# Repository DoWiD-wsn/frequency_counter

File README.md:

# AVR-based Frequency Counter

The AVR-based frequency counter is partly based on the project developed by [Herbert Dingfelder](http://www.herbert-dingfelder.de/?page_id=304) with some extensions and modifications.
It contains an ATmega8 responsible for measuring the frequency of a square-wave applied to one of four input channels (selectable by software) and acting as a TWI slave (I2C).
With the current design, frequencies of up to 50 MHz are measurable with a precision of 10 Hz.

The AVR-based frequency counter was developed and used as part of the [Embedded Testbench (ETB)](https://github.com/DoWiD-wsn/embedded_testbench) where it was used to measure the frequency stability of the internal clock of microcontroller units of embedded systems under different conditions such as ambient temperature and supply voltage level.

For more information on the PCB (and its design) refer to [docs/pcb_design.md](docs/pcb_design.md).

## Directory structure

```
.
├── docs                : documents
│   ├── datasheets      : datasheets of used components
│   └── pcb_design.md   : information on the PCB design
├── kicad               : KiCad files
├── media               : Miscellaneous media (images, etc.)
│   ├── evaluation      : Image of a first prototype evaluation
│   ├── i2c             : I2C register format
│   ├── pcb             : Photos and rendered images of the PCB
│   └── schematic       : SVG images of the schematics
└── source              : C code sources for the ATmega8
```

## Contents

* [Description](#description)
* [Built with](#built-with)
* [Preparation](#preparation)
* [I2C Interface](#i2c-interface)
* [Evaluation](#evaluation)
* [Contributors](#contributors)
* [Changelog](#changelog)
* [License](#license)

## Description

**Schematic** (draft):  

The ATmega8 is clocked with an external quartz crystal with a frequency of 4.096 MHz.
This clock signal is also used to generate a gate-enable signal for the actual frequency counting stage.
To do so, the 4.096 MHz are first divided by a 74HC4040 with a factor of 2^12 (4096) to get a 1 kHz signal that is further divided by a second 74HC4040 with a factor of 2^8 (256) to have an enable signal with a frequency of 3.90625 Hz (corresponds to an enable time of 128 ms (high level)).

The 74HC153 is used to select between four different input channels.
During the 128 ms long high period of the second 74HC4040, the signal of at the selected input channel is forwarded to the third 74HC4040.
That third 74HC4040 forms together with the ATmega8 the actual counting part, that is, both components together form a 24-bit counter that counts the number of periods of the selected input signal during the 128 ms long enable period.
Thereby, the lower 8-bit (fast portion) are counted by the 74HC4040 and, since the eight bit (Q7) triggers the ATmega8' internal 16-bit counter module, the higher 16-bit are counted internally by the ATmega8.
As the 128 ms enable signal is also connected to the external interrupt (INT0) of the ATmega8, the ATmega8 is "informed" whenever a counting period has finished and can then calculate the corresponding frequency of the input signal.
To do so, the 24-bit counter (lower 8-bit read via GPIOs and the higher 16-bit available interally) show how many periods have passed in the last 128 ms and, thus, allow to easily calculate the resulting frequency.

The measured frequency is output via the UART debug interface (default: 8N1 @9600baud).
As the ATmega8 is configured as an I2C slave (address to be defined in software; default: `0x24`), the result can also be obtained via I2C.
Additionally, the I2C interface can be used to configure the basic operation of the frequency counter such as:

* result resolution (Hz, kHz, or MHz)
* input channel (CH0, CH1, CH2, or CH3)
* sampling rate (no sampling, 3 samples, 5 samples, or 10 samples)

Additionally, the result ready flag can be read indicating whether a result is already available.
In case required, also a counter reset (clearing of all registers) can be requested via I2C.

## Built with

The entire code only depends on the basic AVR libraries (i.e., AVR libc) and can be easily compiled with the AVR GCC.
To upload the binary to the ATmega8, the [AVR-ISP](https://www.mikrocontroller.net/articles/AVR_In_System_Programmer) can be used in combination with [AVRdude](https://www.nongnu.org/avrdude/) or similar.

* [avr-gcc 5.4.0](https://gcc.gnu.org/wiki/avr-gcc) - C code library
* [avr-libc 2.0.0](https://www.nongnu.org/avr-libc/) - C code library

## Preparation

Aside from the hardware circuit, it is important to properly set the fuses of the used ATmega8.
The fuses take care of a basic configuration of the ATmega8, or more precisely, they define the clock source and some interfacing options.
For the AVR-based frequency counter, we choose to have an external crystal oscillator and at startup we will give it some clock cycles to become stable.
As stated in the [ATmega8 datasheet](https://www.microchip.com/wwwproducts/en/ATmega8), we need to have the clock selection fuses `CKSEL` set to `1111` and the start-up times fuses `SUT` set to `11`, resulting in the `low fuse byte` to be set to `0xFF` (Note: the fuse bits are active low, i.e. programmed=0, unprogrammed=1; see also [AVR Fuse Calculator](http://eleccelerator.com/fusecalc/fusecalc.php?chip=atmega8)).

In the `high fuse byte`, we leave the boot size selection bits enabled, i.e., `BOOTSZ` is `00`, and we keep the serial programming and data downloading `SPIEN` enabled (otherwise we would not be able to use the [AVR ISP](https://www.mikrocontroller.net/articles/AVR_In_System_Programmer) to flash our firmware).
Additionally, we need to program the oscillator options fuse `CKOPT` to `0` to switch the crystal from weak amplitude to full amplitude required to clock the [74HC4040](https://www.ti.com/product/SN74HC4040) counter.
As a result, we need to set the `high fuse byte` to `0xC9`.

The fuse bit values and the resulting bit pattern as well as the corresponding [AVRDUDE](https://www.nongnu.org/avrdude/) commands can be derived with one of the available [online fuse calculator](https://www.engbedded.com/fusecalc/).
In our case, the resulting AVRDUDE arguments are:  
  `-U lfuse:w:0xff:m -U hfuse:w:0xc9:m`

## I2C Interface

The AVR-based frequency counter can be used as an I2C slave.
The I2C address can be defined in software (default: 0x24).

Basically, there are four 8-bit registers available and accessible via I2C, that are:

1. Configuration register `CONFIG` (address: `0x00`; R/W)
2. Frequency LSB register `FREQ-LSB` (address: `0x01`; R)
3. Frequency MSB register `FREQ-MSB` (address: `0x02`; R)
4. Frequency extended MSB register `FREQ-XMSB` (address: `0x03`; R)

As can be seen, all registers can be read but only the `CONFIG` register allows overwriting its value; the measured frequency value can only be read.

With the `CONFIG` register, the basic operation of the frequency counter can be defined, that is, requesting a software reset, checking the result ready flag, setting the sampling rate, defining the frequency resolution, and selecting the input channel (see figure below).
The default value of the `CONFIG` register is `0x00`.

### Reset request

The reset request bit can be used to cause a software reset of the frequency counter, that is, all counter modules and internal counter values are reset.
The configuration is not changed.

| `RST` | Effect        |
|-------|---------------|
| `0`   | no effect     |
| `1`   | request reset |

### Result ready

The result ready flag indicates whether a frequency measurement is ready to be read.

| `RDY` | Meaning              |
|-------|----------------------|
| `0`   | result not available |
| `1`   | result available     |

### Result sampling

The frequency counter offers to possibility to sample several measurements and provide the mean average to have more stable results.
Thereby, one of four different sampling options can be selected.

| `SMP1` | `SMP0` | Sampling             |
|--------|--------|----------------------|
| `0`    | `0`    | no sampling          |
| `0`    | `1`    | 3 samples            |
| `1`    | `0`    | 5 samples            |
| `1`    | `1`    | 10 samples           |

### Result resolution

The resulting frequency can be read in three different resolution.

| `RES1` | `RES0` | Resolution (result width) |
|--------|--------|---------------------------|
| `0`    | `0`    | Hz (24 bit: LSB+MSB+XMSB) |
| `0`    | `1`    | kHz (16 bit: LSB+MSB)     |
| `1`    | `0`    | MHz (8 bit: LSB)          |
| `1`    | `1`    | reserved                  |

### Input channel selection

With the `CHSEL` bits, the input channel can be selected, that is, the channel that is latched through by the 4-to-1 multiplexer.

| `CHSEL1` | `CHSEL0` | Channel |
|----------|----------|---------|
| `0`      | `0`      | CH0     |
| `0`      | `1`      | CH1     |
| `1`      | `0`      | CH2     |
| `1`      | `1`      | CH3     |

## Evaluation

The concept was evaluated based on a prototype as shown below.
In this prototype, the multiplexer was neglected and the input signal was connected to the counting stage via a jumper.

To check the proper functioning of the prototype, a second microcontroller was used that output its internal clock source via a GPIO pin (the AVR offer to output the clock source to a GPIO named `CLKO`).
In this test setup, the clock source of the microcontroller under test was changed every few seconds between four different clock options:

1. internal 8MHz RC oscillator (Fcpu = 8MHz)
2. internal 8MHz RC oscillator with a prescaler of 8 (Fcpu = 1MHz)
3. external 16MHz quartz oscillator (Fcpu = 16MHz)
4. external 16MHz quartz oscillator with a prescaler of 8 (Fcpu = 2MHz)

These measurements were confirmed with an oscilloscope that also measured the frequency.
Thereby, the expected accuracy of 10Hz could be confirmed.

## Contributors

* **Dominik Widhalm** - [***DC-RES***](https://informatics.tuwien.ac.at/doctoral/resilient-embedded-systems/) - [*UAS Technikum Wien*](https://embsys.technikum-wien.at/staff/widhalm/)

Contributions of any kind to improve the project are highly welcome.
For coding bugs or minor improvements simply use pull requests.
However, for major changes or general discussions please contact [Dominik Widhalm](mailto:widhalm@technikum-wien.at?subject=frequency%20counter%20on%20GitHub).

## Changelog

A list of prior versions and changes between the updates can be found inn the [CHANGELOG.md](CHANGELOG.md) file.
Note that the major and minor number refer to the hardware version of the ASN(x) board while the patch version is used to denote subsequent software versions.

## License

This project is licensed under the MIT License - see the [LICENSE.md](LICENSE.md) file for details.

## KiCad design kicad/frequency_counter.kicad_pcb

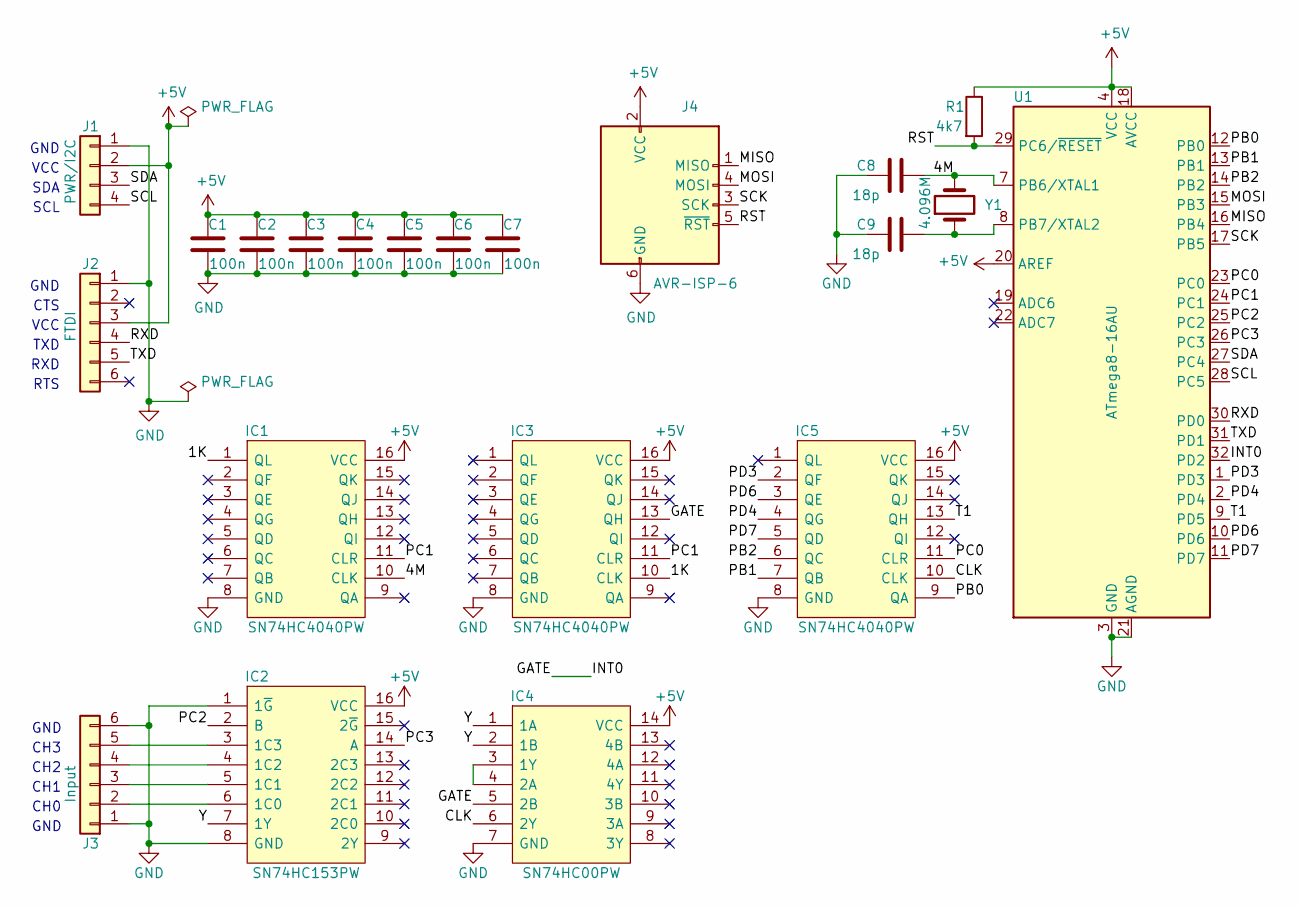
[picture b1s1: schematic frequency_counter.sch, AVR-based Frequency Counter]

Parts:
C1, C2, C3, C4, C5, C6, C7: 100n; C_0603_1608Metric
C8, C9: 18p; C_0603_1608Metric
IC1, IC3, IC5: SN74HC4040PW; SOP65P640X120-16N
IC2: SN74HC153PW; SOP65P640X120-16N
IC4: SN74HC00PW; SOP65P640X120-14N
J1: PWR/I2C; PinHeader_1x04_P2.54mm_Vertical
J2: FTDI; PinHeader_1x06_P2.54mm_Vertical
J3: Input; PinHeader_1x06_P2.54mm_Vertical
J4: AVR-ISP-6; PinHeader_2x03_P2.54mm_Vertical
R1: 4k7; R_0603_1608Metric
U1: ATmega8-16AU; TQFP-32_7x7mm_P0.8mm
Y1: 4.096M; Crystal_SMD_HC49-SD

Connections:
+5V: C1.2, C2.2, C3.2, C4.2, C5.2, C6.2, C7.2, IC1.16 (VCC), IC2.16 (VCC), IC3.16 (VCC), IC4.14 (VCC), IC5.16 (VCC), J1.2, J2.3, J4.2 (VCC), R1.1, U1.4 (VCC), U1.6 (VCC), U1.18 (AVCC), U1.20 (AREF)
/1K: IC1.1 (QL), IC3.10 (CLK)
/4M: C8.1, IC1.10 (CLK), U1.7 (PB6/XTAL1), Y1.2
/CLK: IC4.6 (2Y), IC5.10 (CLK)
/GATE: IC3.13 (QH), IC4.5 (2B), U1.32 (PD2)
/MISO: J4.1 (MISO), U1.16 (PB4)
/MOSI: J4.4 (MOSI), U1.15 (PB3)
/PB0: IC5.9 (QA), U1.12 (PB0)
/PB1: IC5.7 (QB), U1.13 (PB1)
/PB2: IC5.6 (QC), U1.14 (PB2)
/PC0: IC5.11 (CLR), U1.23 (PC0)
/PC1: IC1.11 (CLR), IC3.11 (CLR), U1.24 (PC1)
/PC2: IC2.2 (B), U1.25 (PC2)
/PC3: IC2.14 (A), U1.26 (PC3)
/PD3: IC5.2 (QF), U1.1 (PD3)
/PD4: IC5.4 (QG), U1.2 (PD4)
/PD6: IC5.3 (QE), U1.10 (PD6)
/PD7: IC5.5 (QD), U1.11 (PD7)
/RST: J4.5 (~RST), R1.2, U1.29 (PC6/~RESET)
/RXD: J2.4, U1.30 (PD0)
/SCK: J4.3 (SCK), U1.17 (PB5)
/SCL: J1.4, U1.28 (PC5)
/SDA: J1.3, U1.27 (PC4)
/T1: IC5.13 (QH), U1.9 (PD5)
/TXD: J2.5, U1.31 (PD1)
/Y: IC2.7 (1Y), IC4.1 (1A), IC4.2 (1B)
GND: C1.1, C2.1, C3.1, C4.1, C5.1, C6.1, C7.1, C8.2, C9.2, IC1.8 (GND), IC2.1 (1~G), IC2.8 (GND), IC3.8 (GND), IC4.7 (GND), IC5.8 (GND), J1.1, J2.1, J3.1, J3.6, J4.6 (GND), U1.3 (GND), U1.5 (GND), U1.21 (AGND)
unnamed: C9.1, U1.8 (PB7/XTAL2), Y1.1
unnamed: IC2.3 (1C3), J3.5
unnamed: IC2.4 (1C2), J3.4
unnamed: IC2.5 (1C1), J3.3
unnamed: IC2.6 (1C0), J3.2
unnamed: IC4.3 (1Y), IC4.4 (2A)

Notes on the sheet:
GND
CH0
CTS
VCC
TXD
RXD
RTS
SDA
SCL
CH1
CH2
CH3

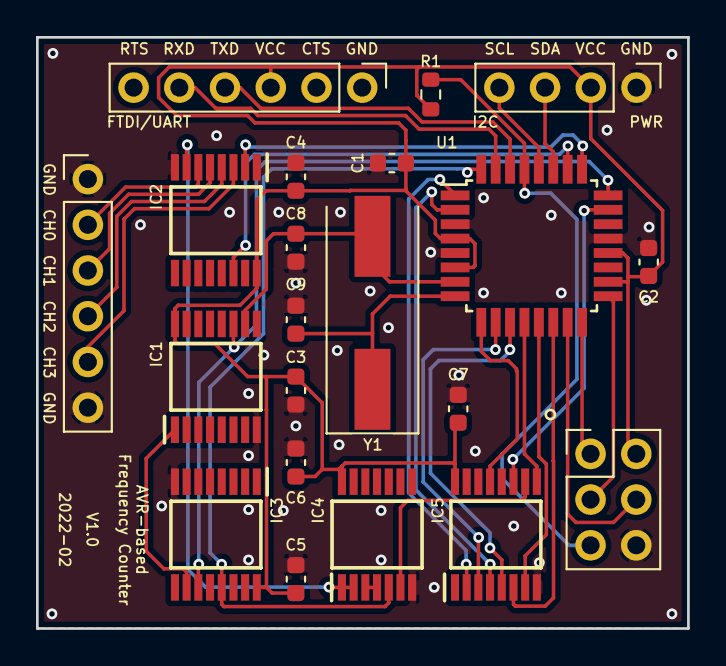
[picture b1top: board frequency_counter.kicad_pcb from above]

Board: 2 copper layers, 36.2 x 32.8 mm, 21 parts (0 on the bottom side), 33 nets.

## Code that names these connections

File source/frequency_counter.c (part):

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#define GPIO_PRESCALER_RST_DDR      (DDRC)
#define GPIO_PRESCALER_RST_PORT     (PORTC)
#define GPIO_PRESCALER_RST_PIN      (PINC)
#define GPIO_PRESCALER_RST          _BV(PC1)
/* Frequency-Counter Reset */
#define GPIO_CNT_RST_DDR            (DDRC)
#define GPIO_CNT_RST_PORT           (PORTC)
#define GPIO_CNT_RST_PIN            (PINC)
#define GPIO_CNT_RST                _BV(PC0)
/* MUX Select */
#define GPIO_MUX_DDR                (DDRC)
#define GPIO_MUX_PORT               (PORTC)
#define GPIO_MUX_PIN                (PINC)
#define GPIO_MUX_S0                 _BV(PC3)
#define GPIO_MUX_S1                 _BV(PC2)

/*** Gate-enable Clock ***/
#define GPIO_GATE_EN_DDR            (DDRD)
#define GPIO_GATE_EN_PORT           (PORTD)
#define GPIO_GATE_EN_PIN            (PIND)
#define GPIO_GATE_EN                _BV(PD2)

/*** Frequency Counter Value ***/
/* Q7 (T1) */
#define GPIO_CNT_Q7_DDR             (DDRD)
#define GPIO_CNT_Q7_PORT            (PORTD)
#define GPIO_CNT_Q7_PIN             (PIND)
#define GPIO_CNT_Q7                 _BV(PD5)
/* Q6 */
#define GPIO_CNT_Q6_DDR             (DDRD)
#define GPIO_CNT_Q6_PORT            (PORTD)
#define GPIO_CNT_Q6_PIN             (PIND)
#define GPIO_CNT_Q6                 _BV(PD4)
/* Q5 */
#define GPIO_CNT_Q5_DDR             (DDRD)
#define GPIO_CNT_Q5_PORT            (PORTD)
#define GPIO_CNT_Q5_PIN             (PIND)
#define GPIO_CNT_Q5                 _BV(PD3)
/* Q4 */
#define GPIO_CNT_Q4_DDR             (DDRD)
#define GPIO_CNT_Q4_PORT            (PORTD)
#define GPIO_CNT_Q4_PIN             (PIND)
#define GPIO_CNT_Q4                 _BV(PD6)
/* Q3 */
#define GPIO_CNT_Q3_DDR             (DDRD)
#define GPIO_CNT_Q3_PORT            (PORTD)
#define GPIO_CNT_Q3_PIN             (PIND)
#define GPIO_CNT_Q3                 _BV(PD7)
/* Q2 */
#define GPIO_CNT_Q2_DDR             (DDRB)
#define GPIO_CNT_Q2_PORT            (PORTB)
#define GPIO_CNT_Q2_PIN             (PINB)
#define GPIO_CNT_Q2                 _BV(PB2)
/* Q1 */
#define GPIO_CNT_Q1_DDR             (DDRB)
#define GPIO_CNT_Q1_PORT            (PORTB)
#define GPIO_CNT_Q1_PIN             (PINB)
#define GPIO_CNT_Q1                 _BV(PB1)
/* Q0 */
#define GPIO_CNT_Q0_DDR             (DDRB)
#define GPIO_CNT_Q0_PORT            (PORTB)
#define GPIO_CNT_Q0_PIN             (PINB)
#define GPIO_CNT_Q0                 _BV(PB0)


/***** GLOBAL VARIABLES ***********************************************/
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
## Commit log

2021-10-15 Initial commit: added superior gitignore
2021-10-15 Added initial README as well as LICENSE and CHANGELOG
2021-10-15 Added media files and datasheets
2021-10-15 Added latest sources (not fully tested/working yet)
2021-10-15 Added background to schematic; added part description
2021-10-15 Added evaluation description in README
2021-10-15 Added I2C slave description to README
2021-10-15 Added background to I2C CONFIG reg figure
2021-10-15 Added TOC to README
2021-10-15 Fixed TOC in README
2021-10-15 Added notes and todos for further improvement
2021-11-18 Changed license file extension to markdown
2022-02-26 Added initial PCB design
2022-02-26 Removed unintentional artefacts in 3D PCB visualization
2022-02-26 Updated directory structure description in README
2022-02-28 Updated PCB design Added board measurements Removed temp/cache files
2022-06-21 Minor typo fixes
